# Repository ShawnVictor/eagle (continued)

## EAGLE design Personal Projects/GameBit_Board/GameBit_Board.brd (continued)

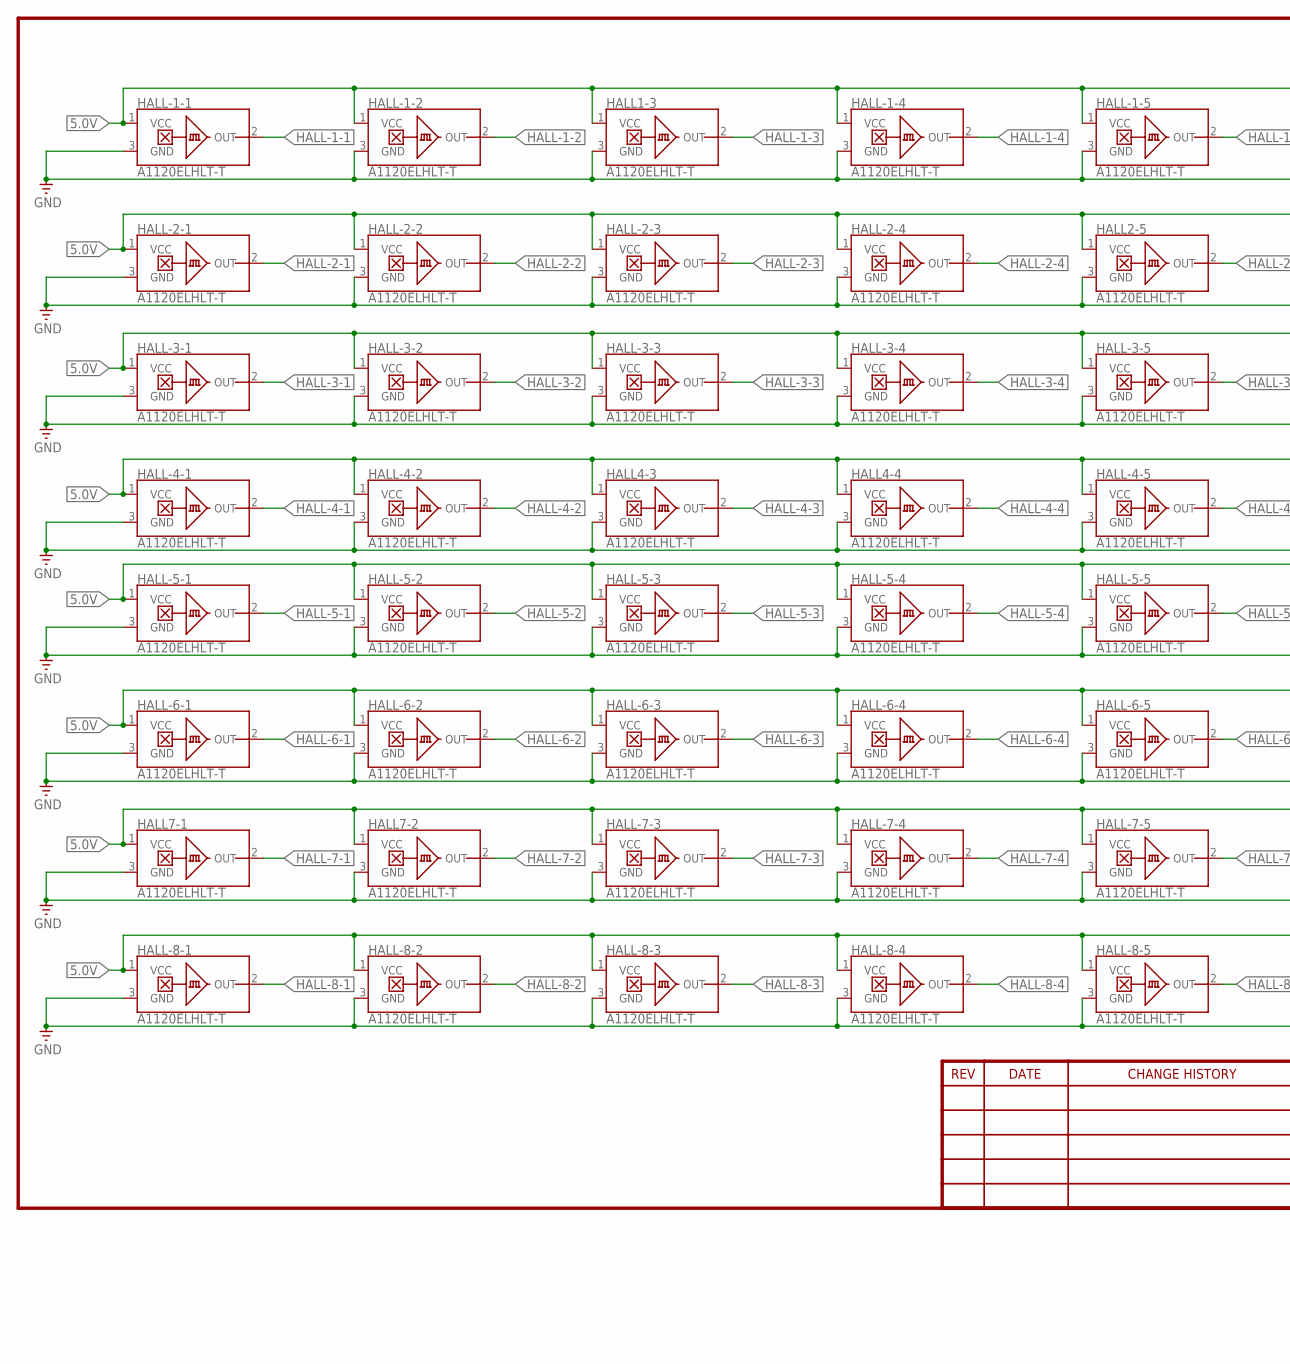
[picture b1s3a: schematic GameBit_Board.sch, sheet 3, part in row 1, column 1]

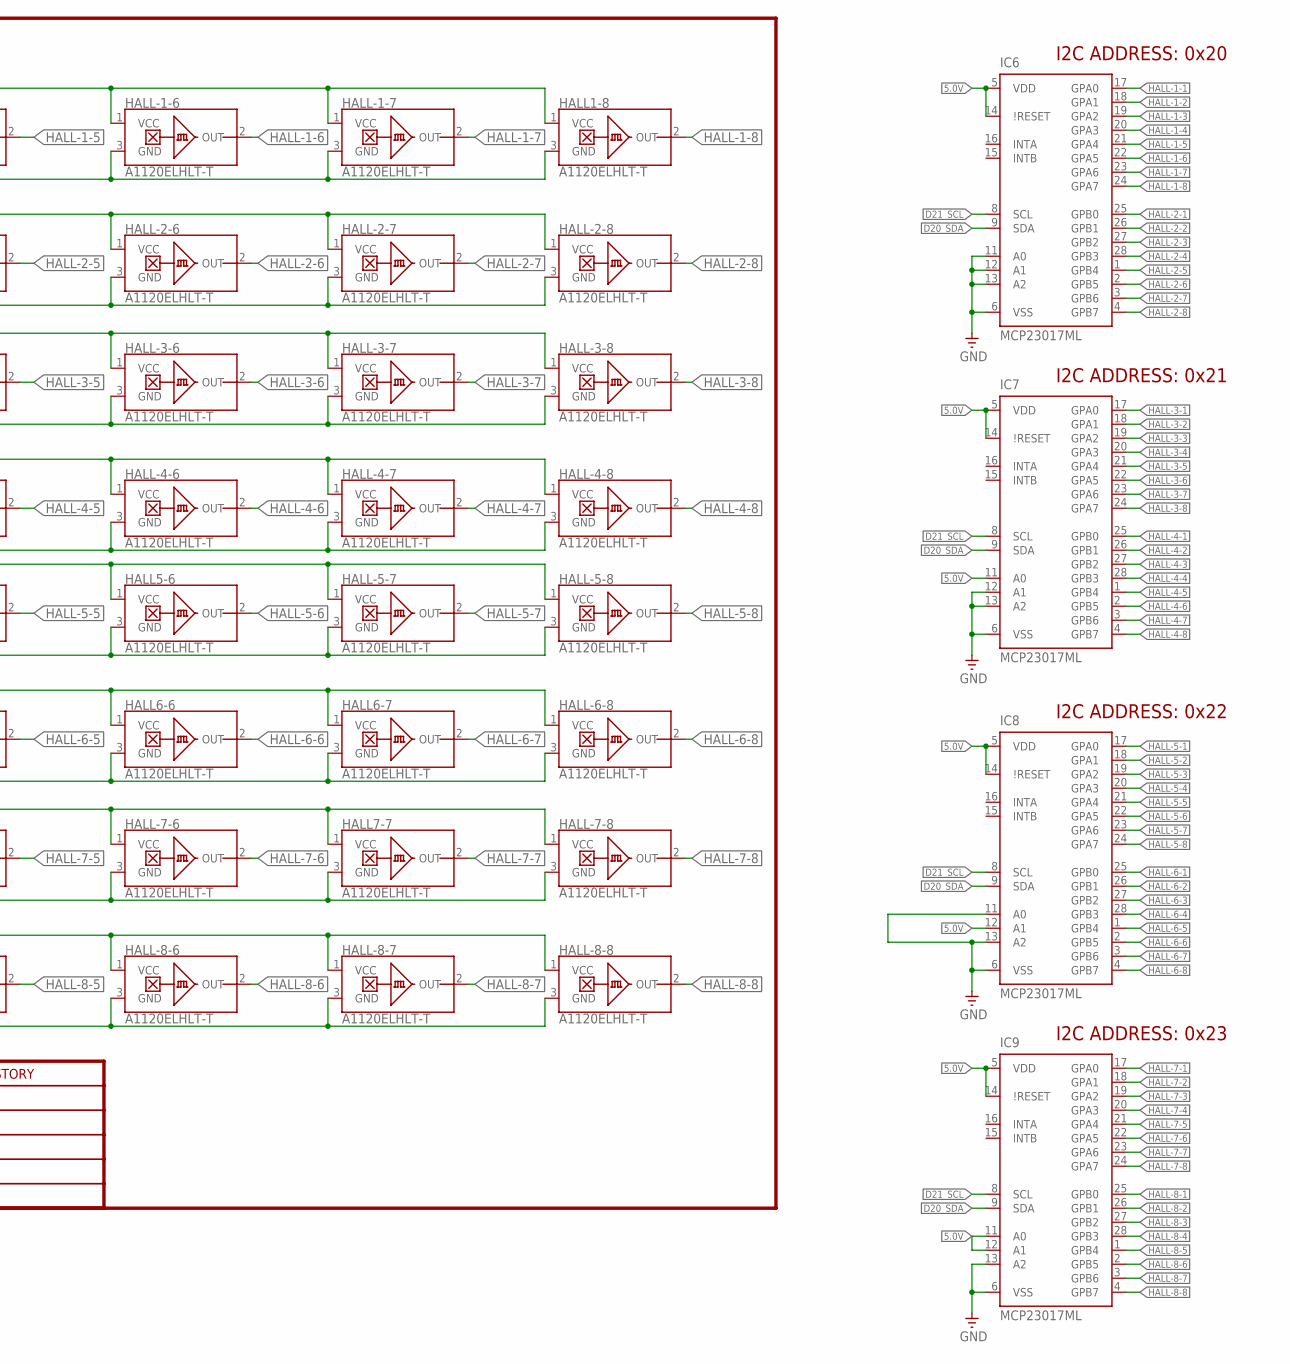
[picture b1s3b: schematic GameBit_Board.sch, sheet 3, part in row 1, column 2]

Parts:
HALL1-3, HALL1-8, HALL2-5, HALL4-3, HALL4-4, HALL5-6, HALL6-6, HALL6-7, HALL7-1, HALL7-2, HALL7-7: A1120ELHLT-T; SOT95P290X110-3N
HALL-1-1, HALL-1-2, HALL-1-4, HALL-1-5, HALL-1-6, HALL-1-7, HALL-2-1, HALL-2-2, HALL-2-3, HALL-2-4, HALL-2-6, HALL-2-7, HALL-2-8, HALL-3-1, HALL-3-2, HALL-3-3, HALL-3-4, HALL-3-5, HALL-3-6, HALL-3-7, HALL-3-8, HALL-4-1, HALL-4-2, HALL-4-5, HALL-4-6, HALL-4-7, HALL-4-8, HALL-5-1, HALL-5-2, HALL-5-3, HALL-5-4, HALL-5-5, HALL-5-7, HALL-5-8, HALL-6-1, HALL-6-2, HALL-6-3, HALL-6-4, HALL-6-5, HALL-6-8, HALL-7-3, HALL-7-4, HALL-7-5, HALL-7-6, HALL-7-8, HALL-8-1, HALL-8-2, HALL-8-3, HALL-8-4, HALL-8-5, HALL-8-6, HALL-8-7, HALL-8-8: A1120ELHLT-T; SOT95P290X110-3N
IC6, IC7, IC8, IC9: MCP23017ML; QFN28-ML_6X6MM

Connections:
5.0V: HALL1-3.1 (VCC), HALL1-8.1 (VCC), HALL2-5.1 (VCC), HALL4-3.1 (VCC), HALL4-4.1 (VCC), HALL5-6.1 (VCC), HALL6-6.1 (VCC), HALL6-7.1 (VCC), HALL7-1.1 (VCC), HALL7-2.1 (VCC), HALL7-7.1 (VCC), HALL-1-1.1 (VCC), HALL-1-2.1 (VCC), HALL-1-4.1 (VCC), HALL-1-5.1 (VCC), HALL-1-6.1 (VCC), HALL-1-7.1 (VCC), HALL-2-1.1 (VCC), HALL-2-2.1 (VCC), HALL-2-3.1 (VCC), HALL-2-4.1 (VCC), HALL-2-6.1 (VCC), HALL-2-7.1 (VCC), HALL-2-8.1 (VCC), HALL-3-1.1 (VCC), HALL-3-2.1 (VCC), HALL-3-3.1 (VCC), HALL-3-4.1 (VCC), HALL-3-5.1 (VCC), HALL-3-6.1 (VCC), HALL-3-7.1 (VCC), HALL-3-8.1 (VCC), HALL-4-1.1 (VCC), HALL-4-2.1 (VCC), HALL-4-5.1 (VCC), HALL-4-6.1 (VCC), HALL-4-7.1 (VCC), HALL-4-8.1 (VCC), HALL-5-1.1 (VCC), HALL-5-2.1 (VCC), HALL-5-3.1 (VCC), HALL-5-4.1 (VCC), HALL-5-5.1 (VCC), HALL-5-7.1 (VCC), HALL-5-8.1 (VCC), HALL-6-1.1 (VCC), HALL-6-2.1 (VCC), HALL-6-3.1 (VCC), HALL-6-4.1 (VCC), HALL-6-5.1 (VCC), HALL-6-8.1 (VCC), HALL-7-3.1 (VCC), HALL-7-4.1 (VCC), HALL-7-5.1 (VCC), HALL-7-6.1 (VCC), HALL-7-8.1 (VCC), HALL-8-1.1 (VCC), HALL-8-2.1 (VCC), HALL-8-3.1 (VCC), HALL-8-4.1 (VCC), HALL-8-5.1 (VCC), HALL-8-6.1 (VCC), HALL-8-7.1 (VCC), HALL-8-8.1 (VCC), IC6.5 (VDD), IC6.14 (\!RESET), IC7.5 (VDD), IC7.11 (A0), IC7.14 (\!RESET), IC8.5 (VDD), IC8.12 (A1), IC8.14 (\!RESET), IC9.5 (VDD), IC9.11 (A0), IC9.12 (A1), IC9.14 (\!RESET); also elsewhere on the board
D20_SDA: IC6.9 (SDA), IC7.9 (SDA), IC8.9 (SDA), IC9.9 (SDA); also elsewhere on the board
D21_SCL: IC6.8 (SCL), IC7.8 (SCL), IC8.8 (SCL), IC9.8 (SCL); also elsewhere on the board
GND: HALL1-3.3 (GND), HALL1-8.3 (GND), HALL2-5.3 (GND), HALL4-3.3 (GND), HALL4-4.3 (GND), HALL5-6.3 (GND), HALL6-6.3 (GND), HALL6-7.3 (GND), HALL7-1.3 (GND), HALL7-2.3 (GND), HALL7-7.3 (GND), HALL-1-1.3 (GND), HALL-1-2.3 (GND), HALL-1-4.3 (GND), HALL-1-5.3 (GND), HALL-1-6.3 (GND), HALL-1-7.3 (GND), HALL-2-1.3 (GND), HALL-2-2.3 (GND), HALL-2-3.3 (GND), HALL-2-4.3 (GND), HALL-2-6.3 (GND), HALL-2-7.3 (GND), HALL-2-8.3 (GND), HALL-3-1.3 (GND), HALL-3-2.3 (GND), HALL-3-3.3 (GND), HALL-3-4.3 (GND), HALL-3-5.3 (GND), HALL-3-6.3 (GND), HALL-3-7.3 (GND), HALL-3-8.3 (GND), HALL-4-1.3 (GND), HALL-4-2.3 (GND), HALL-4-5.3 (GND), HALL-4-6.3 (GND), HALL-4-7.3 (GND), HALL-4-8.3 (GND), HALL-5-1.3 (GND), HALL-5-2.3 (GND), HALL-5-3.3 (GND), HALL-5-4.3 (GND), HALL-5-5.3 (GND), HALL-5-7.3 (GND), HALL-5-8.3 (GND), HALL-6-1.3 (GND), HALL-6-2.3 (GND), HALL-6-3.3 (GND), HALL-6-4.3 (GND), HALL-6-5.3 (GND), HALL-6-8.3 (GND), HALL-7-3.3 (GND), HALL-7-4.3 (GND), HALL-7-5.3 (GND), HALL-7-6.3 (GND), HALL-7-8.3 (GND), HALL-8-1.3 (GND), HALL-8-2.3 (GND), HALL-8-3.3 (GND), HALL-8-4.3 (GND), HALL-8-5.3 (GND), HALL-8-6.3 (GND), HALL-8-7.3 (GND), HALL-8-8.3 (GND), IC6.6 (VSS), IC6.11 (A0), IC6.12 (A1), IC6.13 (A2), IC7.6 (VSS), IC7.12 (A1), IC7.13 (A2), IC8.6 (VSS), IC8.11 (A0), IC8.13 (A2), IC9.6 (VSS), IC9.13 (A2); also elsewhere on the board
HALL-1-1: HALL-1-1.2 (OUT), IC6.17 (GPA0)
HALL-1-2: HALL-1-2.2 (OUT), IC6.18 (GPA1)
HALL-1-3: HALL1-3.2 (OUT), IC6.19 (GPA2)
HALL-1-4: HALL-1-4.2 (OUT), IC6.20 (GPA3)
HALL-1-5: HALL-1-5.2 (OUT), IC6.21 (GPA4)
HALL-1-6: HALL-1-6.2 (OUT), IC6.22 (GPA5)
HALL-1-7: HALL-1-7.2 (OUT), IC6.23 (GPA6)
HALL-1-8: HALL1-8.2 (OUT), IC6.24 (GPA7)
HALL-2-1: HALL-2-1.2 (OUT), IC6.25 (GPB0)
HALL-2-2: HALL-2-2.2 (OUT), IC6.26 (GPB1)
HALL-2-3: HALL-2-3.2 (OUT), IC6.27 (GPB2)
HALL-2-4: HALL-2-4.2 (OUT), IC6.28 (GPB3)
HALL-2-5: HALL2-5.2 (OUT), IC6.1 (GPB4)
HALL-2-6: HALL-2-6.2 (OUT), IC6.2 (GPB5)
HALL-2-7: HALL-2-7.2 (OUT), IC6.3 (GPB6)
HALL-2-8: HALL-2-8.2 (OUT), IC6.4 (GPB7)
HALL-3-1: HALL-3-1.2 (OUT), IC7.17 (GPA0)
HALL-3-2: HALL-3-2.2 (OUT), IC7.18 (GPA1)
HALL-3-3: HALL-3-3.2 (OUT), IC7.19 (GPA2)
HALL-3-4: HALL-3-4.2 (OUT), IC7.20 (GPA3)
HALL-3-5: HALL-3-5.2 (OUT), IC7.21 (GPA4)
HALL-3-6: HALL-3-6.2 (OUT), IC7.22 (GPA5)
HALL-3-7: HALL-3-7.2 (OUT), IC7.23 (GPA6)
HALL-3-8: HALL-3-8.2 (OUT), IC7.24 (GPA7)
HALL-4-1: HALL-4-1.2 (OUT), IC7.25 (GPB0)
HALL-4-2: HALL-4-2.2 (OUT), IC7.26 (GPB1)
HALL-4-3: HALL4-3.2 (OUT), IC7.27 (GPB2)
HALL-4-4: HALL4-4.2 (OUT), IC7.28 (GPB3)
HALL-4-5: HALL-4-5.2 (OUT), IC7.1 (GPB4)
HALL-4-6: HALL-4-6.2 (OUT), IC7.2 (GPB5)
HALL-4-7: HALL-4-7.2 (OUT), IC7.3 (GPB6)
HALL-4-8: HALL-4-8.2 (OUT), IC7.4 (GPB7)
HALL-5-1: HALL-5-1.2 (OUT), IC8.17 (GPA0)
HALL-5-2: HALL-5-2.2 (OUT), IC8.18 (GPA1)
HALL-5-3: HALL-5-3.2 (OUT), IC8.19 (GPA2)
HALL-5-4: HALL-5-4.2 (OUT), IC8.20 (GPA3)
HALL-5-5: HALL-5-5.2 (OUT), IC8.21 (GPA4)
HALL-5-6: HALL5-6.2 (OUT), IC8.22 (GPA5)
HALL-5-7: HALL-5-7.2 (OUT), IC8.23 (GPA6)
HALL-5-8: HALL-5-8.2 (OUT), IC8.24 (GPA7)
HALL-6-1: HALL-6-1.2 (OUT), IC8.25 (GPB0)
HALL-6-2: HALL-6-2.2 (OUT), IC8.26 (GPB1)
HALL-6-3: HALL-6-3.2 (OUT), IC8.27 (GPB2)
HALL-6-4: HALL-6-4.2 (OUT), IC8.28 (GPB3)
HALL-6-5: HALL-6-5.2 (OUT), IC8.1 (GPB4)
HALL-6-6: HALL6-6.2 (OUT), IC8.2 (GPB5)
HALL-6-7: HALL6-7.2 (OUT), IC8.3 (GPB6)
HALL-6-8: HALL-6-8.2 (OUT), IC8.4 (GPB7)
HALL-7-1: HALL7-1.2 (OUT), IC9.17 (GPA0)
HALL-7-2: HALL7-2.2 (OUT), IC9.18 (GPA1)
HALL-7-3: HALL-7-3.2 (OUT), IC9.19 (GPA2)
HALL-7-4: HALL-7-4.2 (OUT), IC9.20 (GPA3)
HALL-7-5: HALL-7-5.2 (OUT), IC9.21 (GPA4)
HALL-7-6: HALL-7-6.2 (OUT), IC9.22 (GPA5)
HALL-7-7: HALL7-7.2 (OUT), IC9.23 (GPA6)
HALL-7-8: HALL-7-8.2 (OUT), IC9.24 (GPA7)
HALL-8-1: HALL-8-1.2 (OUT), IC9.25 (GPB0)
HALL-8-2: HALL-8-2.2 (OUT), IC9.26 (GPB1)
HALL-8-3: HALL-8-3.2 (OUT), IC9.27 (GPB2)
HALL-8-4: HALL-8-4.2 (OUT), IC9.28 (GPB3)
HALL-8-5: HALL-8-5.2 (OUT), IC9.1 (GPB4)
HALL-8-6: HALL-8-6.2 (OUT), IC9.2 (GPB5)
HALL-8-7: HALL-8-7.2 (OUT), IC9.3 (GPB6)
HALL-8-8: HALL-8-8.2 (OUT), IC9.4 (GPB7)

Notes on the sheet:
I2C ADDRESS: 0x20
I2C ADDRESS: 0x21
I2C ADDRESS: 0x22
I2C ADDRESS: 0x23

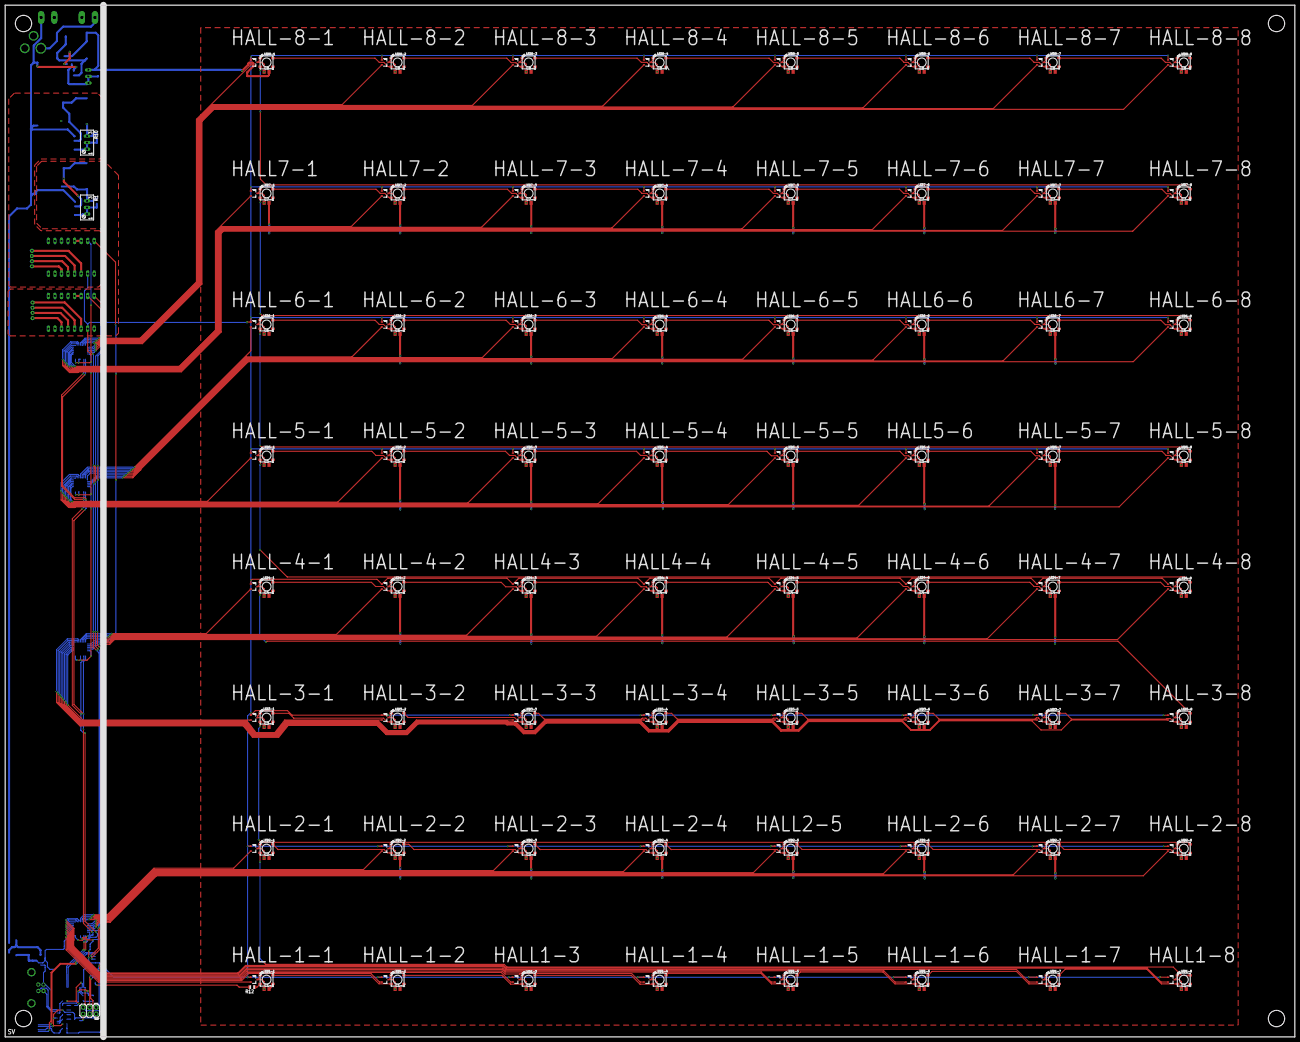
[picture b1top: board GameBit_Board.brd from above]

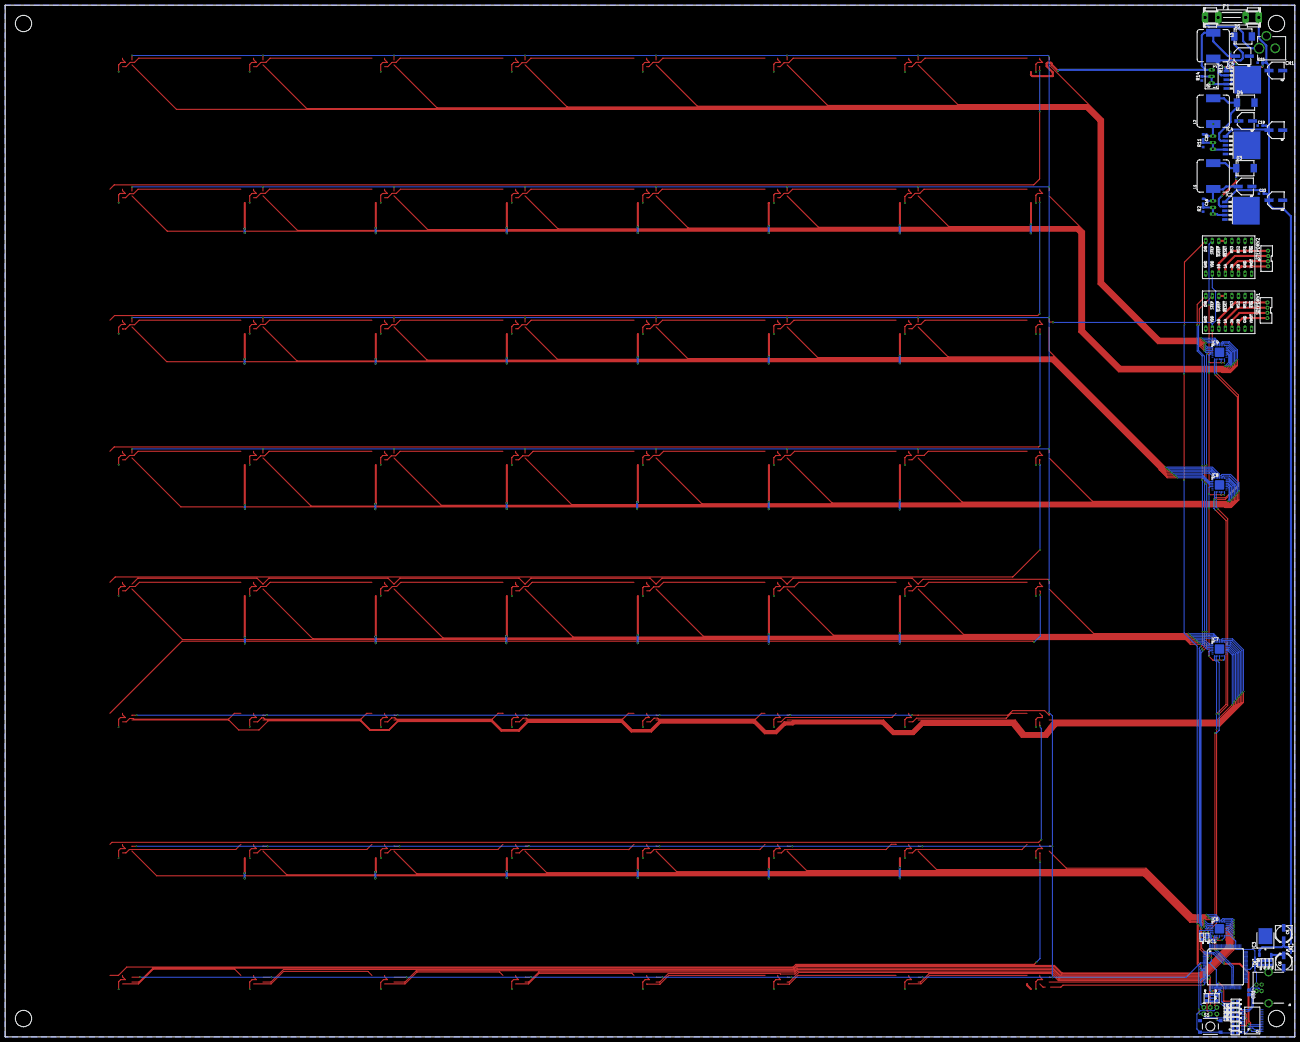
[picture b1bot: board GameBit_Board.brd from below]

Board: 2 copper layers, 500.0 x 400.0 mm, 262 parts (66 on the bottom side), 180 nets.

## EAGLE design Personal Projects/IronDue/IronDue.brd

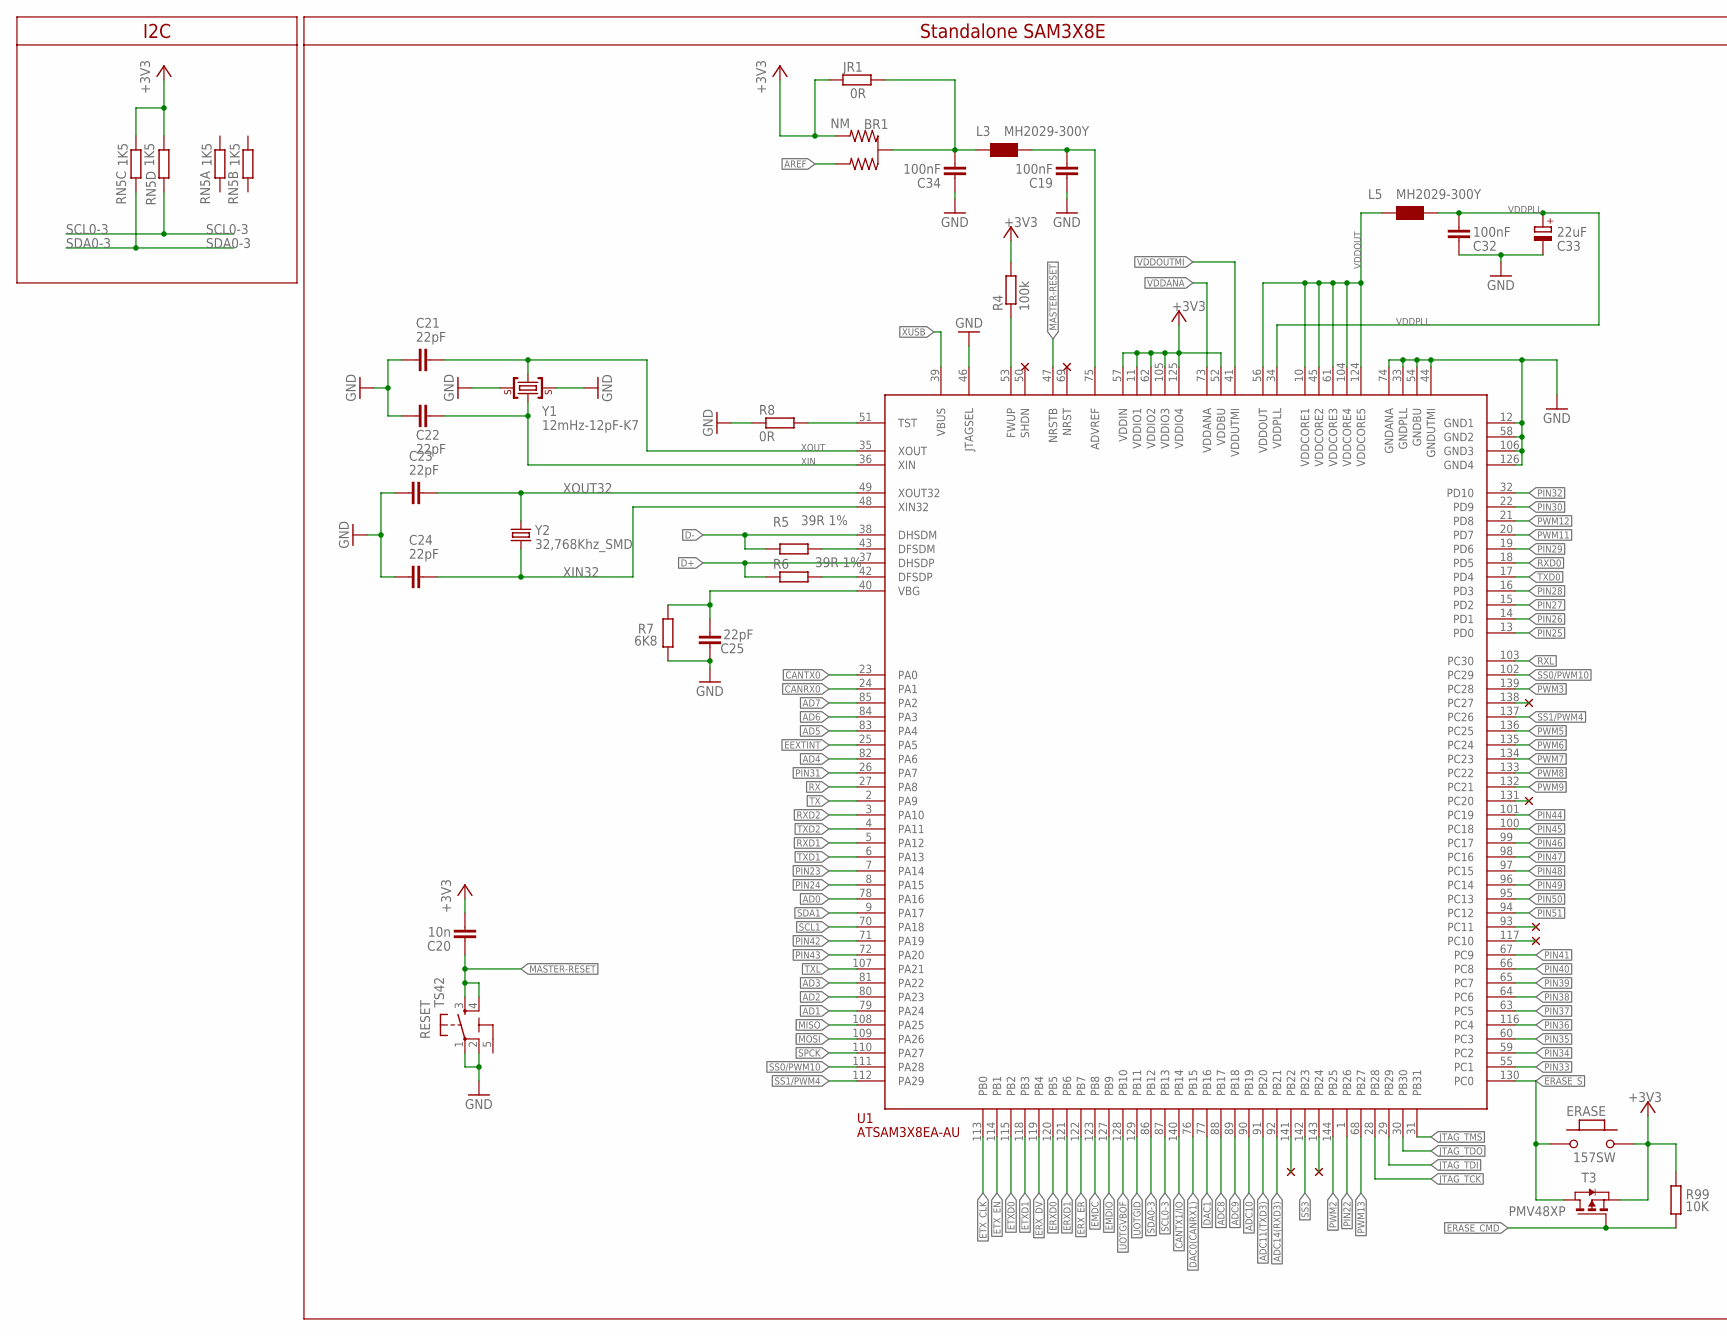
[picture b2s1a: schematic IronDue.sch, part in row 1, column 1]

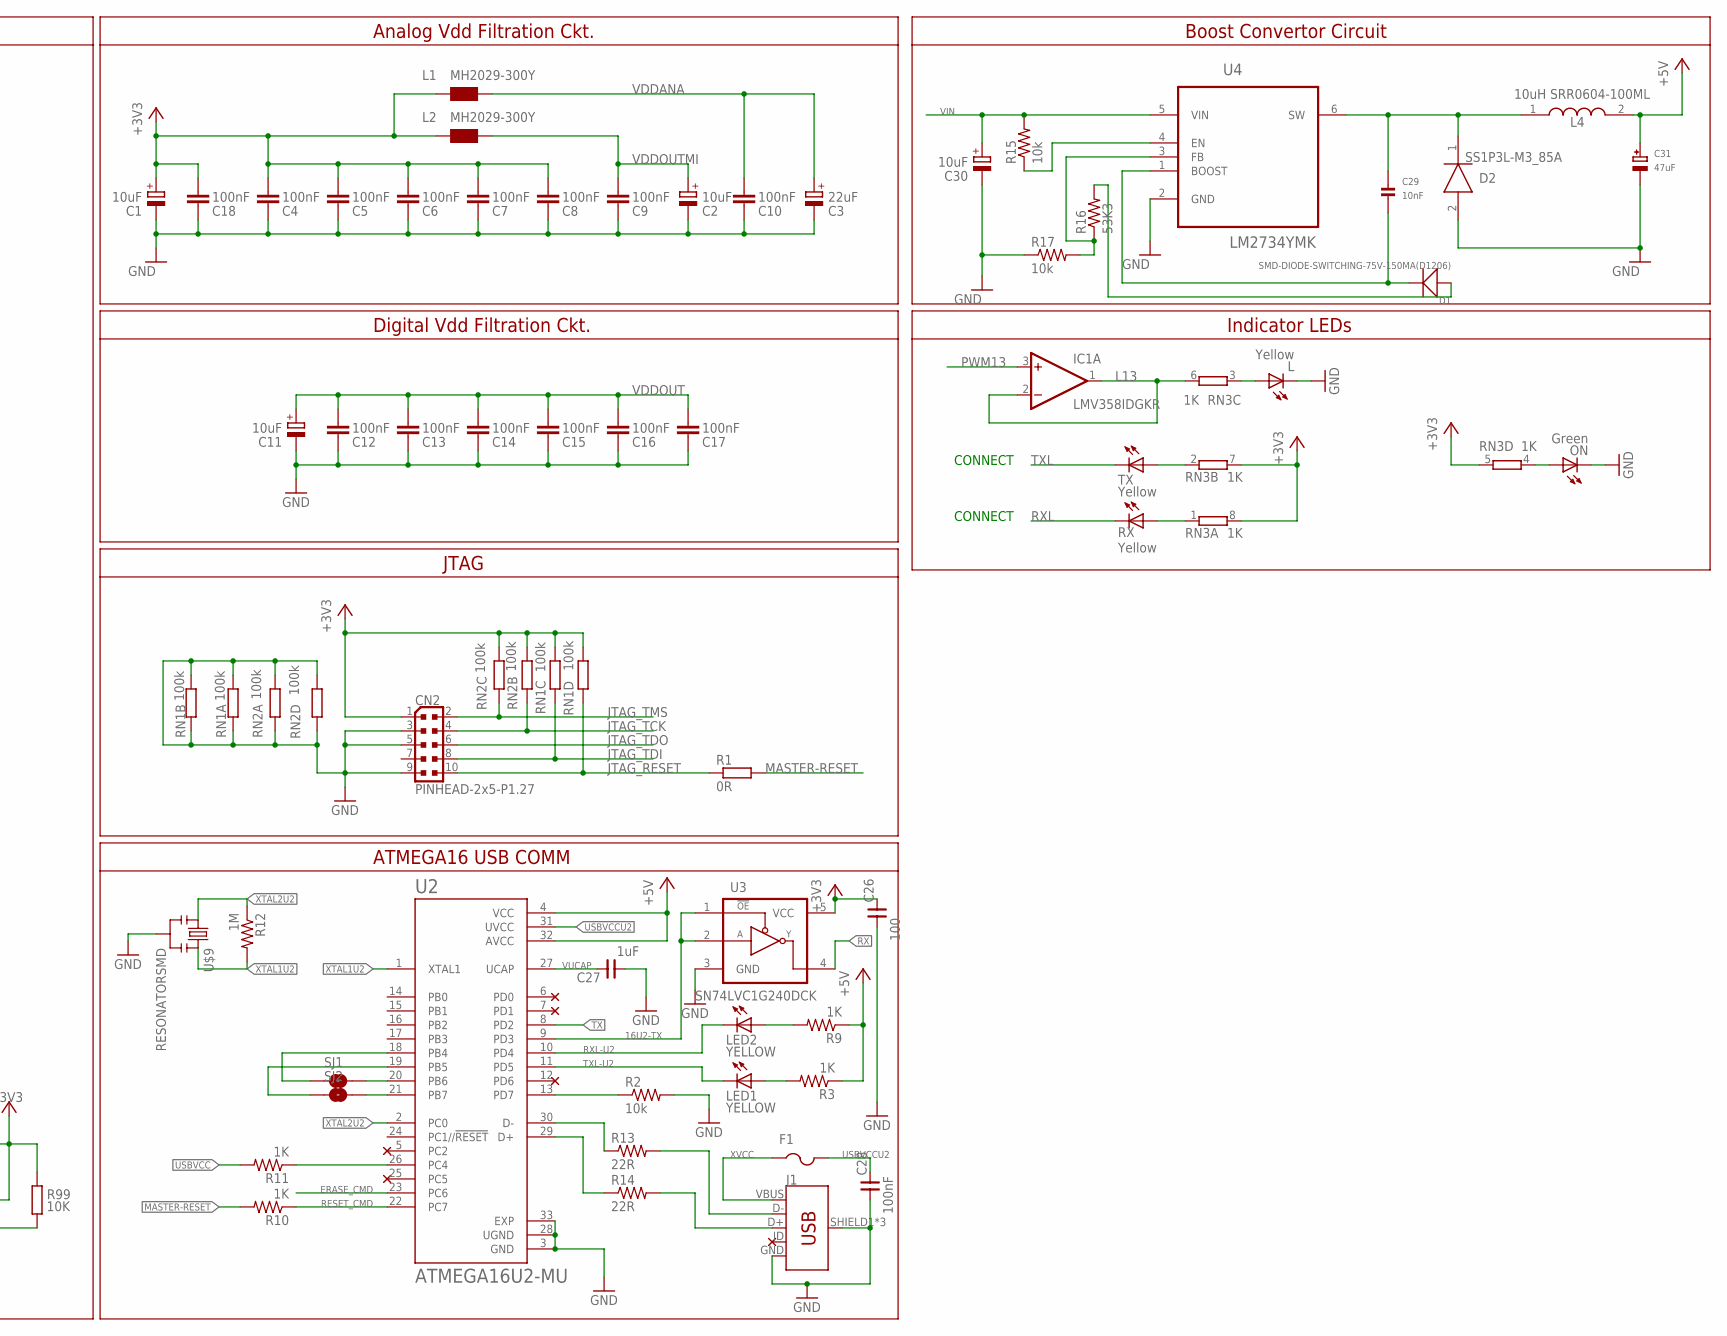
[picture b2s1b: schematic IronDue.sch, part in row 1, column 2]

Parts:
BR1: NM; J0402
C1, C2, C11, C30: 10uF; SMC_B
C3, C33: 22uF; SMC_B
C4, C5, C6, C7, C8, C9, C10, C12, C13, C14, C15, C16, C17, C18, C19, C32, C34: 100nF; C0402
C20: 10n; C0402
C21, C22, C23, C24, C25: 22pF; C0402
C26: 100; 0402
C27: 1uF; 0402
C28: 100nF; 0402
C29: 10nF; 0402
C31: 47uF; PANASONIC_D
CN2: PINHEAD-2x5-P1.27; PINHEAD_2X05_127
D1: SMD-DIODE-SWITCHING-75V-150MA(D1206); LED-1206
D2: SS1P3L-M3_85A; SMP
ERASE: 157SW; SMD_157SW
F1: MF-MSMF050-2 500mA; 1812
IC1: LMV358IDGKR; MSOP08
J1: USB_MICRO-BREDUCED_PASTE; USB-B-MICRO-SMD_RED_PASTE
JR1: 0R; R0402
L: Yellow; CHIPLED_0805
L1, L2, L3, L5: MH2029-300Y; 0805
L4: 10uH SRR0604-100ML; SRR0604-SERIES
LED1, LED2: YELLOW; CHIPLED_0805
ON: Green; CHIPLED_0805
R1, R8: 0R; R0402
R2, R15: 10k; R0402
R3, R9, R10, R11: 1K; R0402
R4: 100k; R0402
R5, R6: 39R 1%; R0402
R7: 6K8; R0603-ROUND
R12: 1M; R0402
R13, R14: 22R; R0402
R16: 53K3; R0603
R17: 10k; R0603
R99: 10K; R0402
RESET: TS42
RN1, RN2: 100k; CAY16
RN3: 1K; CAY16
RN5: 1K5; CAY16
RX: Yellow; CHIPLED_0805
SJ1, SJ2: SOLDERJUMPERNO; SJ_2S-NO
T3: PMV48XP; SOT-23
TX: Yellow; CHIPLED_0805
U1: ATSAM3X8EA-AU; LQFP144
U2: ATMEGA16U2-MU; QFN50P500X500X100-33N
U3: SN74LVC1G240DCK; SC70-5
U4: LM2734YMK; SOT95P285X100-6N
U$1, U$2, U$3, U$4, U$5, U$6, U$7, U$8, U$10, U$11, U$12, U$13, U$14, U$15: NC
U$9: RESONATORSMD; RESONATOR-SMD
Y1: 12mHz-12pF-K7; CRYSTAL-3.2-2.5
Y2: 32,768Khz_SMD; RESONATOR_EPSON_FC_145

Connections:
5-GND: RESET.5 (5-GND)
16U2-TX: U2.9 (PD3), U3.1 (OE#), U3.2 (A)
+3V3: BR1.3 (2), C1.+, C4.2, C5.2, C6.2, C7.2, C8.2, C18.2, C20.2, C26.2, CN2.1, ERASE.1, JR1.1, L1.1, L2.1, R4.2, R99.2, RN1.5 (2), RN1.6 (2), RN2.2 (1), RN2.3 (1), RN3.5 (2), RN3.7 (2), RN3.8 (2), RN5.3 (1), RN5.4 (1), T3.2 (S), U1.11 (VDDIO1), U1.52 (VDDBU), U1.57 (VDDIN), U1.62 (VDDIO2), U1.105 (VDDIO3), U1.125 (VDDIO4), U3.5 (VCC)
+5V: C31.+, L4.2, R3.1, R9.1, U2.4 (VCC), U2.32 (AVCC)
AD0: U1.78 (PA16)
AD1: U1.79 (PA24)
AD2: U1.80 (PA23)
AD3: U1.81 (PA22)
AD4: U1.82 (PA6)
AD5: U1.83 (PA4)
AD6: U1.84 (PA3)
AD7: U1.85 (PA2)
ADC8: U1.88 (PB17)
ADC9: U1.89 (PB18)
ADC10: U1.90 (PB19)
ADC11(TXD3): U1.91 (PB20)
ADC14(RXD3): U1.92 (PB21)
AREF: BR1.1
CANRX0: U1.24 (PA1)
CANTX0: U1.23 (PA0)
CANTX1/IO: U1.140 (PB14)
D+: R6.1, U1.37 (DHSDP)
D-: R5.1, U1.38 (DHSDM)
DAC0(CANRX1): U1.76 (PB15)
DAC1: U1.77 (PB16)
EEXTINT: U1.25 (PA5)
EMDC: U1.123 (PB8)
EMDIO: U1.127 (PB9)
ERASE_CMD: R99.1, T3.3 (G), U2.23 (PC6)
ERASE_S: ERASE.2, T3.1 (D), U1.130 (PC0)
ERXD0: U1.120 (PB5)
ERXD1: U1.121 (PB6)
ERX_DV: U1.119 (PB4)
ERX_ER: U1.122 (PB7)
ETXD0: U1.115 (PB2)
ETXD1: U1.118 (PB3)
ETX_CLK: U1.113 (PB0)
ETX_EN: U1.114 (PB1)
GND: C1.-, C2.-, C3.-, C4.1, C5.1, C6.1, C7.1, C8.1, C9.1, C10.1, C11.-, C12.1, C13.1, C14.1, C15.1, C16.1, C17.1, C18.1, C19.1, C21.2, C22.2, C23.2, C24.2, C25.2, C26.1, C27.1, C28.1, C30.-, C31.-, C32.1, C33.-, C34.1, CN2.3, CN2.5, CN2.9, D2.2 (K), J1.GND, J1.SHIELD1 (SHIELD), J1.SHIELD2 (SHIELD), J1.SHIELD3 (SHIELD), L.C, ON.C, R2.2, R7.1, R8.1, R17.1, RESET.1, RESET.2, RN1.1, RN1.2 (1), RN1.7 (2), RN1.8 (2), RN2.1, RN2.4 (1), RN2.5 (2), RN2.8 (2), U1.12 (GND1), U1.33 (GNDPLL), U1.44 (GNDUTMI), U1.46 (JTAGSEL), U1.54 (GNDBU), U1.58 (GND2), U1.74 (GNDANA), U1.106 (GND3), U1.126 (GND4), U2.3 (GND), U2.28 (UGND), U2.33 (EXP), U3.3 (GND), U4.2 (GND), U$9.2, Y1.2 (GND), Y1.4 (GND)
JTAG_RESET: CN2.10, R1.1, RN1.4 (1)
JTAG_TCK: CN2.4, RN2.7 (2), U1.28 (PB28)
JTAG_TDI: CN2.8, RN1.3 (1), U1.29 (PB29)
JTAG_TDO: CN2.6, U1.30 (PB30)
JTAG_TMS: CN2.2, RN2.6 (2), U1.31 (PB31)
L13: IC1.1 (OUT), IC1.2 (-IN), RN3.6 (2)
MASTER-RESET: C20.1, R1.2, R10.2, RESET.3, RESET.4, U1.47 (NRSTB)
MISO: U1.108 (PA25)
MOSI: U1.109 (PA26)
unnamed: R4.1, U1.53 (FWUP)
unnamed: C19.2, L3.2, U1.75 (ADVREF)
unnamed: BR1.2 (C), C34.2, JR1.2, L3.1
unnamed: ON.A, RN3.4 (1)
unnamed: L.A, RN3.3 (1)
unnamed: R8.2, U1.51 (TST)
unnamed: R6.2, U1.42 (DFSDP)
unnamed: R5.2, U1.43 (DFSDM)
unnamed: C25.1, R7.2, U1.40 (VBG)
unnamed: R2.1, U2.13 (PD7)
unnamed: LED2.A, R9.2
unnamed: LED1.A, R3.2
unnamed: R11.1, U2.26 (PC4)
unnamed: R13.1, U2.30 (D-)
unnamed: R14.1, U2.29 (D+)
unnamed: J1.D+, R14.2
unnamed: J1.D-, R13.2
unnamed: C29.2, D1.-, U4.1 (BOOST)
unnamed: R16.1, R17.2, U4.3 (FB)
unnamed: SJ1.2, U2.20 (PB6)
unnamed: SJ2.2, U2.21 (PB7)
unnamed: SJ1.1, U2.18 (PB4)
unnamed: SJ2.1, U2.19 (PB5)
unnamed: C29.1, D2.1 (A), L4.1, U4.6 (SW)
unnamed: D1.+, R16.2
unnamed: R15.1, U4.4 (EN)
unnamed: RN3.1, RX.A
unnamed: RN3.2 (1), TX.A
PIN22: U1.1 (PB26)
PIN23: U1.7 (PA14)
PIN24: U1.8 (PA15)
PIN25: U1.13 (PD0)
PIN26: U1.14 (PD1)
PIN27: U1.15 (PD2)
PIN28: U1.16 (PD3)
PIN29: U1.19 (PD6)
PIN30: U1.22 (PD9)
PIN31: U1.26 (PA7)
PIN32: U1.32 (PD10)
PIN33: U1.55 (PC1)
PIN34: U1.59 (PC2)
PIN35: U1.60 (PC3)
PIN36: U1.116 (PC4)
PIN37: U1.63 (PC5)
PIN38: U1.64 (PC6)
PIN39: U1.65 (PC7)
PIN40: U1.66 (PC8)
PIN41: U1.67 (PC9)
PIN42: U1.71 (PA19)
PIN43: U1.72 (PA20)
PIN44: U1.101 (PC19)
PIN45: U1.100 (PC18)
PIN46: U1.99 (PC17)
PIN47: U1.98 (PC16)
PIN48: U1.97 (PC15)
PIN49: U1.96 (PC14)
PIN50: U1.95 (PC13)
PIN51: U1.94 (PC12)
PWM2: U1.144 (PB25)
PWM3: U1.139 (PC28)
PWM5: U1.136 (PC25)
PWM6: U1.135 (PC24)
PWM7: U1.134 (PC23)
PWM8: U1.133 (PC22)
PWM9: U1.132 (PC21)
PWM11: U1.20 (PD7)
PWM12: U1.21 (PD8)
PWM13: IC1.3 (+IN), U1.68 (PB27)
RESET_CMD: R10.1, U2.22 (PC7)
RX: U1.27 (PA8), U3.4 (Y)
RXD0: U1.18 (PD5)
RXD1: U1.5 (PA12)
RXD2: U1.3 (PA10)
RXL: RX.C, U1.103 (PC30)
RXL-U2: LED2.C, U2.10 (PD4)
SCL0-3: RN5.5 (2), U1.87 (PB13)
SCL1: U1.70 (PA18)
SDA0-3: RN5.6 (2), U1.86 (PB12)
SDA1: U1.9 (PA17)
SPCK: U1.110 (PA27)
SS0/PWM10: U1.102 (PC29), U1.111 (PA28)
SS1/PWM4: U1.112 (PA29), U1.137 (PC26)
SS3: U1.142 (PB23)
TX: U1.2 (PA9), U2.8 (PD2)
TXD0: U1.17 (PD4)
TXD1: U1.6 (PA13)
TXD2: U1.4 (PA11)
TXL: TX.C, U1.107 (PA21)
TXL-U2: LED1.C, U2.11 (PD5)
UOTGID: U1.129 (PB11)
UOTGVBOF: U1.128 (PB10)
USBVCC: R11.2
USBVCCU2: C28.2, F1.2, U2.31 (UVCC)
V+: IC1.8 (V+)
V-: IC1.4 (V-)
VDDANA: C3.+, C10.2, L1.2, U1.73 (VDDANA)
VDDOUT: C11.+, C12.2, C13.2, C14.2, C15.2, C16.2, C17.2, L5.1, U1.10 (VDDCORE1), U1.45 (VDDCORE2), U1.56 (VDDOUT), U1.61 (VDDCORE3), U1.104 (VDDCORE4), U1.124 (VDDCORE5)
VDDOUTMI: C2.+, C9.2, L2.2, U1.41 (VDDUTMI)
VDDPLL: C32.2, C33.+, L5.2, U1.34 (VDDPLL)
VIN: C30.+, R15.2, U4.5 (VIN)
VUCAP: C27.2, U2.27 (UCAP)
XIN: C22.1, U1.36 (XIN), Y1.1 (C1)
XIN32: C24.1, U1.48 (XIN32), Y2.P$2 (2)
XOUT: C21.1, U1.35 (XOUT), Y1.3 (C2)
XOUT32: C23.1, U1.49 (XOUT32), Y2.P$1 (1)
XTAL1U2: R12.2, U2.1 (XTAL1), U$9.3
XTAL2U2: R12.1, U2.2 (PC0), U$9.1
XUSB: U1.39 (VBUS)
XVCC: F1.1, J1.VBUS

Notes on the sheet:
CONNECT
I2C
Standalone SAM3X8E
Analog Vdd Filtration Ckt.
Digital Vdd Filtration Ckt.
JTAG
ATMEGA16 USB COMM
Indicator LEDs
Boost Convertor Circuit

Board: 2 copper layers, 101 parts (2 on the bottom side), 69 nets, no tracks yet.
